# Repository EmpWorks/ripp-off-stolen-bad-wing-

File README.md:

original designer 
https://github.com/hazels-garage/bad-wings/tree/master/pocket

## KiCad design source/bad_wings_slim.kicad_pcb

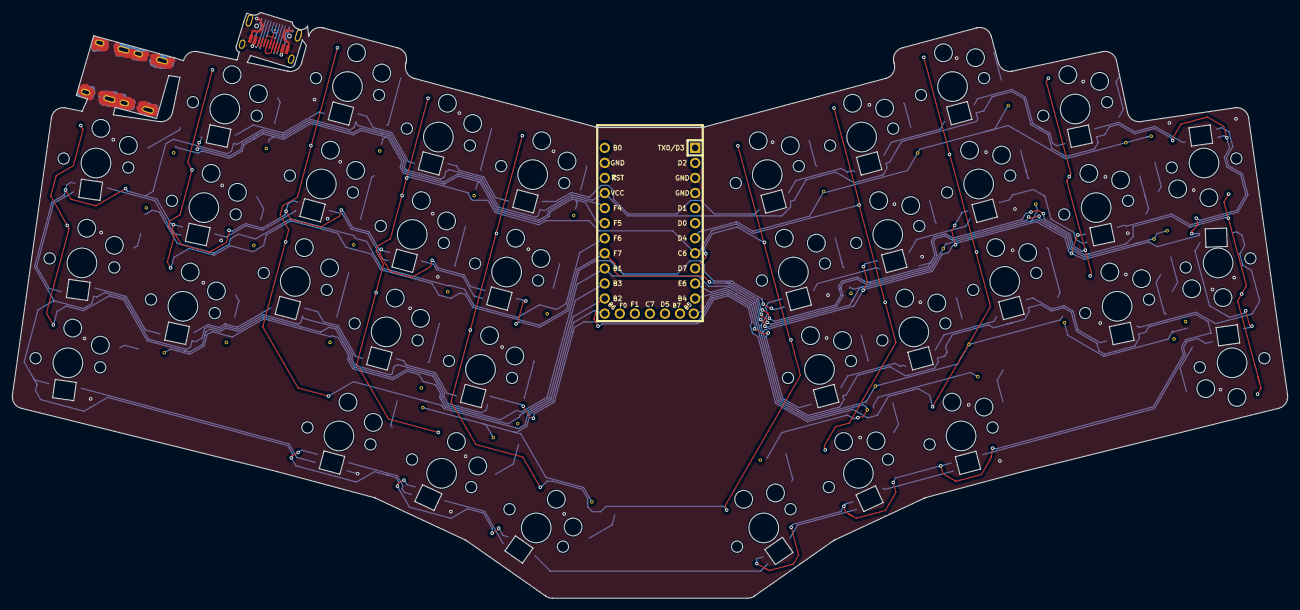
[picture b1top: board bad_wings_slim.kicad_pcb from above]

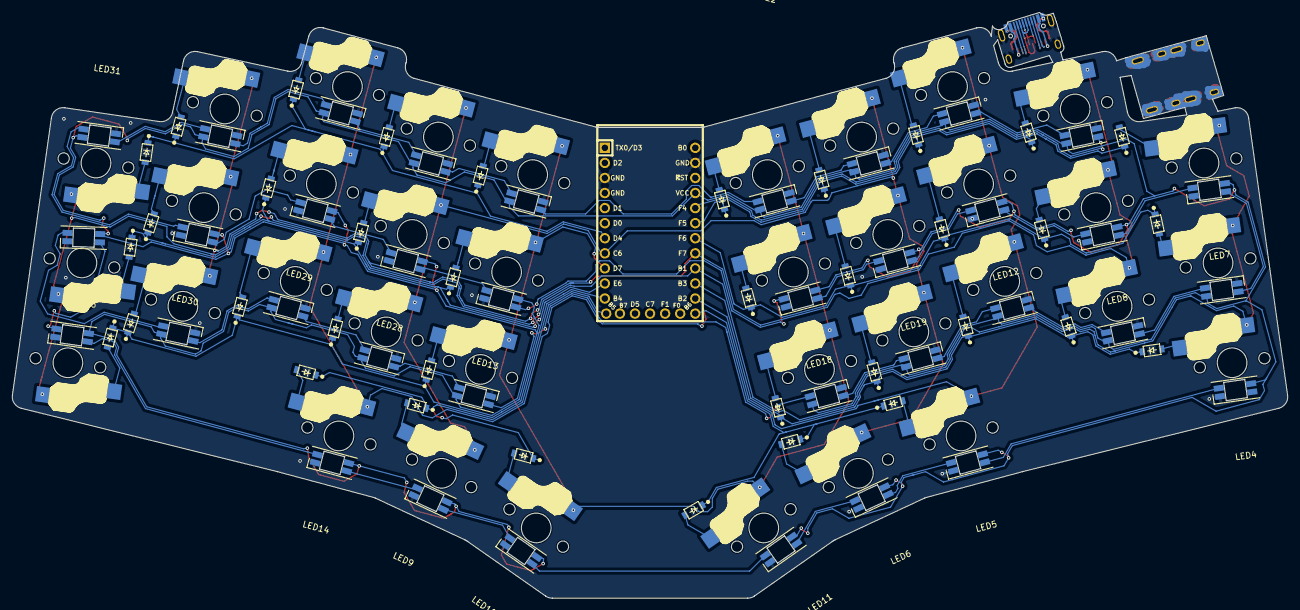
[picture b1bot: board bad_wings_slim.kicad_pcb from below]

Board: 2 copper layers, 214.9 x 98.7 mm, 113 parts (76 on the bottom side), 87 nets.

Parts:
D1, D2, D3, D4, D5, D6, D7, D8, D9, D10, D11, D12, D13, D14, D15, D16, D17, D18, D19, D20, D21, D22, D23, D24, D25, D26, D27, D28, D29, D30, D31, D32, D33, D34, D35, D36: 1N4148W; D_SOD-123
LED4, LED5, LED6, LED7, LED8, LED9, LED10, LED11, LED12, LED13, LED14, LED15, LED16, LED17, LED18, LED19, LED20, LED21, LED22, LED23, LED24, LED25, LED26, LED27, LED28, LED29, LED30, LED31, LED32, LED33, LED34, LED35, LED36, LED37, LED38, LED39: YS-SK6812MINI-E
SW1, SW2, SW3, SW4, SW5, SW6, SW7, SW8, SW9, SW10, SW11, SW12, SW13, SW14, SW15, SW16, SW17, SW18, SW19, SW20, SW21, SW22, SW23, SW24, SW25, SW26, SW27, SW28, SW29, SW30, SW31, SW32, SW33, SW34, SW35, SW36: SW_Push_45deg; ChocV1_V2_Hotswap new
U2: ProMicro; Elite-C-castellated-29pin-holes
USB1, USB1#2, USB1#3, USB1#4: HRO-TYPE-C-31-M-12-Type-C; HRO-TYPE-C-31-M-12-Assembly

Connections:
/col0: SW1.1, SW2.1, SW3.1, SW19.1, SW20.1, SW21.1, U2.16 (B1/15)
/col1: SW4.1, SW5.1, SW6.1, SW22.1, SW23.1, SW24.1, U2.17 (F7/A0)
/col2: SW7.1, SW8.1, SW9.1, SW16.1, SW25.1, SW26.1, SW27.1, SW34.1, U2.14 (B2/16)
/col3: SW10.1, SW11.1, SW12.1, SW17.1, SW28.1, SW29.1, SW30.1, SW35.1, U2.8 (5/C6)
/col4: SW13.1, SW14.1, SW15.1, SW18.1, SW31.1, SW32.1, SW33.1, SW36.1, U2.9 (6/D7)
/row0: D3.1 (K), D6.1 (K), D9.1 (K), D12.1 (K), D15.1 (K), U2.19 (F5/A2)
/row1: D2.1 (K), D5.1 (K), D8.1 (K), D11.1 (K), D14.1 (K), U2.18 (F6/A1)
/row2: D1.1 (K), D4.1 (K), D7.1 (K), D10.1 (K), D13.1 (K), U2.15 (B3/14)
/row3: D16.1 (K), D17.1 (K), D18.1 (K), U2.13 (B6/10)
/row4: D21.1 (K), D24.1 (K), D27.1 (K), D30.1 (K), D33.1 (K), U2.7 (4/D4)
/row5: D20.1 (K), D23.1 (K), D26.1 (K), D29.1 (K), D32.1 (K), U2.10 (7/E6)
/row6: D19.1 (K), D22.1 (K), D25.1 (K), D28.1 (K), D31.1 (K), U2.11 (8/B4)
/row7: D34.1 (K), D35.1 (K), D36.1 (K), U2.12 (9/B5)
GND: LED4.3 (VSS), LED5.3 (VSS), LED6.3 (VSS), LED7.3 (VSS), LED8.3 (VSS), LED9.3 (VSS), LED10.3 (VSS), LED11.3 (VSS), LED12.3 (VSS), LED13.3 (VSS), LED14.3 (VSS), LED15.3 (VSS), LED16.3 (VSS), LED17.3 (VSS), LED18.3 (VSS), LED19.3 (VSS), LED20.3 (VSS), LED21.3 (VSS), LED22.3 (VSS), LED23.3 (VSS), LED24.3 (VSS), LED25.3 (VSS), LED26.3 (VSS), LED27.3 (VSS), LED28.3 (VSS), LED29.3 (VSS), LED30.3 (VSS), LED31.3 (VSS), LED32.3 (VSS), LED33.3 (VSS), LED34.3 (VSS), LED35.3 (VSS), LED36.3 (VSS), LED37.3 (VSS), LED38.3 (VSS), LED39.3 (VSS), U2.3 (GND), U2.4 (GND), U2.23 (GND), USB1.1, USB1.12, USB1#2.13, USB1#3.13, USB1#4.1, USB1#4.12, USB1#4.13
unnamed: D1.2 (A), SW1.2
unnamed: D2.2 (A), SW2.2
unnamed: D3.2 (A), SW3.2
unnamed: D4.2 (A), SW4.2
unnamed: D5.2 (A), SW5.2
unnamed: D6.2 (A), SW6.2
unnamed: D7.2 (A), SW7.2
unnamed: D8.2 (A), SW8.2
unnamed: D9.2 (A), SW9.2
unnamed: D10.2 (A), SW10.2
unnamed: D11.2 (A), SW11.2
unnamed: D12.2 (A), SW12.2
unnamed: D13.2 (A), SW13.2
unnamed: D14.2 (A), SW14.2
unnamed: D15.2 (A), SW15.2
unnamed: D16.2 (A), SW16.2
unnamed: D17.2 (A), SW17.2
unnamed: D18.2 (A), SW18.2
unnamed: D19.2 (A), SW19.2
unnamed: D20.2 (A), SW20.2
unnamed: D21.2 (A), SW21.2
unnamed: D22.2 (A), SW22.2
unnamed: D23.2 (A), SW23.2
unnamed: D24.2 (A), SW24.2
unnamed: D25.2 (A), SW25.2
unnamed: D26.2 (A), SW26.2
unnamed: D27.2 (A), SW27.2
unnamed: D28.2 (A), SW28.2
unnamed: D29.2 (A), SW29.2
unnamed: D30.2 (A), SW30.2
unnamed: D31.2 (A), SW31.2
unnamed: D32.2 (A), SW32.2
unnamed: D33.2 (A), SW33.2
unnamed: D34.2 (A), SW34.2
unnamed: D35.2 (A), SW35.2
unnamed: D36.2 (A), SW36.2
unnamed: LED4.4 (DIN), LED5.2 (DOUT)
unnamed: LED5.4 (DIN), LED6.2 (DOUT)
unnamed: LED7.4 (DIN), LED8.2 (DOUT)
unnamed: LED9.2 (DOUT), LED10.4 (DIN)
unnamed: LED10.2 (DOUT), LED11.4 (DIN)
unnamed: LED6.4 (DIN), LED11.2 (DOUT)
unnamed: LED12.4 (DIN), LED19.2 (DOUT)
unnamed: LED8.4 (DIN), LED12.2 (DOUT)
unnamed: LED13.4 (DIN), LED28.2 (DOUT)
unnamed: LED13.2 (DOUT), LED18.4 (DIN)
unnamed: LED14.4 (DIN), LED15.2 (DOUT)
unnamed: LED9.4 (DIN), LED14.2 (DOUT)
unnamed: LED15.4 (DIN), LED16.2 (DOUT)
unnamed: LED16.4 (DIN), LED17.2 (DOUT)
unnamed: LED17.4 (DIN), LED23.2 (DOUT)
unnamed: LED18.2 (DOUT), LED19.4 (DIN)
unnamed: LED20.4 (DIN), LED24.2 (DOUT)
unnamed: LED20.2 (DOUT), LED21.4 (DIN)
unnamed: LED21.2 (DOUT), LED22.4 (DIN)
unnamed: LED22.2 (DOUT), LED23.4 (DIN)
unnamed: LED24.4 (DIN), LED25.2 (DOUT)
unnamed: LED25.4 (DIN), LED26.2 (DOUT)
unnamed: LED26.4 (DIN), LED27.2 (DOUT)
unnamed: LED7.2 (DOUT), LED27.4 (DIN)
unnamed: LED28.4 (DIN), LED29.2 (DOUT)
unnamed: LED29.4 (DIN), LED30.2 (DOUT)
unnamed: LED30.4 (DIN), LED31.2 (DOUT)
unnamed: LED31.4 (DIN), LED35.2 (DOUT)
unnamed: LED32.4 (DIN), LED36.2 (DOUT)
unnamed: LED32.2 (DOUT), LED33.4 (DIN)
unnamed: LED33.2 (DOUT), LED34.4 (DIN)
unnamed: LED34.2 (DOUT), LED35.4 (DIN)
unnamed: LED36.4 (DIN), LED37.2 (DOUT)
unnamed: LED37.4 (DIN), LED38.2 (DOUT)
unnamed: LED38.4 (DIN), LED39.2 (DOUT)
VCC: LED4.1 (VDD), LED5.1 (VDD), LED6.1 (VDD), LED7.1 (VDD), LED8.1 (VDD), LED9.1 (VDD), LED10.1 (VDD), LED11.1 (VDD), LED12.1 (VDD), LED13.1 (VDD), LED14.1 (VDD), LED15.1 (VDD), LED16.1 (VDD), LED17.1 (VDD), LED18.1 (VDD), LED19.1 (VDD), LED20.1 (VDD), LED21.1 (VDD), LED22.1 (VDD), LED23.1 (VDD), LED24.1 (VDD), LED25.1 (VDD), LED26.1 (VDD), LED27.1 (VDD), LED28.1 (VDD), LED29.1 (VDD), LED30.1 (VDD), LED31.1 (VDD), LED32.1 (VDD), LED33.1 (VDD), LED34.1 (VDD), LED35.1 (VDD), LED36.1 (VDD), LED37.1 (VDD), LED38.1 (VDD), LED39.1 (VDD), U2.21 (VCC)
led: LED39.4 (DIN), U2.20 (F4/A3)

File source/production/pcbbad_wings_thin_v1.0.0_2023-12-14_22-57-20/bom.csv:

Designator,Footprint,Quantity,Value,LCSC Part #
"D1, D10, D11, D12, D13, D14, D15, D16, D17, D18, D19, D2, D20, D21, D22, D23, D24, D25, D26, D27, D28, D29, D3, D30, D31, D32, D33, D34, D35, D36, D4, D5, D6, D7, D8, D9",D_SOD-123,36,1N4148W,
"LED10, LED11, LED12, LED13, LED14, LED15, LED16, LED17, LED18, LED19, LED20, LED21, LED22, LED23, LED24, LED25, LED26, LED27, LED28, LED29, LED30, LED31, LED32, LED33, LED34, LED35, LED36, LED37, LED38, LED39, LED4, LED5, LED6, LED7, LED8, LED9",YS-SK6812MINI-E,36,YS-SK6812MINI-E,
"SW1, SW10, SW11, SW12, SW13, SW14, SW15, SW16, SW17, SW18, SW19, SW2, SW20, SW21, SW22, SW23, SW24, SW25, SW26, SW27, SW28, SW29, SW3, SW30, SW31, SW32, SW33, SW34, SW35, SW36, SW4, SW5, SW6, SW7, SW8, SW9",ChocV1_V2_Hotswap new,36,SW_Push_45deg,
U2,Elite-C-castellated-29pin-holes,1,ProMicro,
"USB1_4, USB1_3, USB1_2, USB1",HRO-TYPE-C-31-M-12-Assembly,4,HRO-TYPE-C-31-M-12-Type-C,
